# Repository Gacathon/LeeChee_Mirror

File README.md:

# Lisence

CC BY-NC-SA 3.0

# LeeChee_Mirror
Cherry G80&amp;G81-1800 Keyboard layout.Almost both sides place switch.

# Recommend
Please read Readme.docx before assembling.

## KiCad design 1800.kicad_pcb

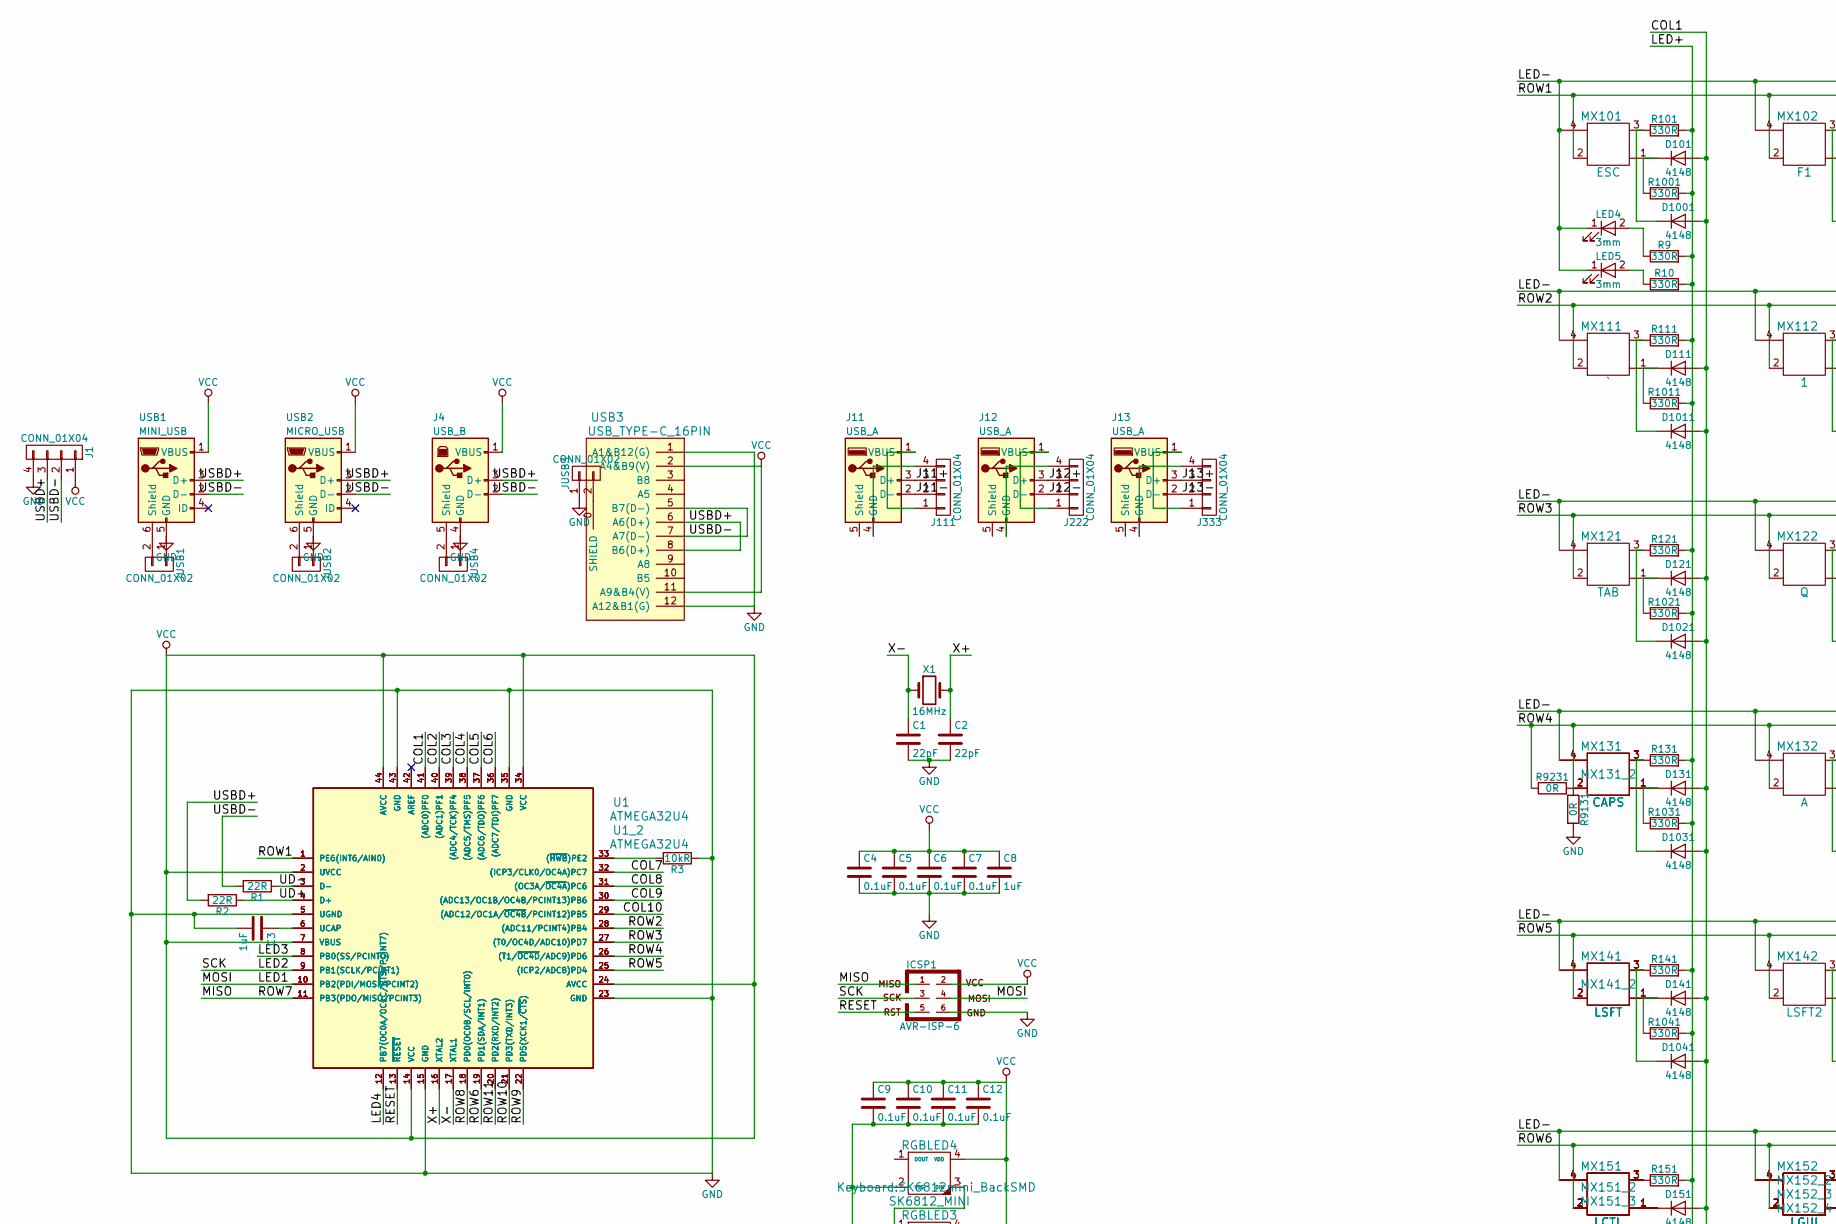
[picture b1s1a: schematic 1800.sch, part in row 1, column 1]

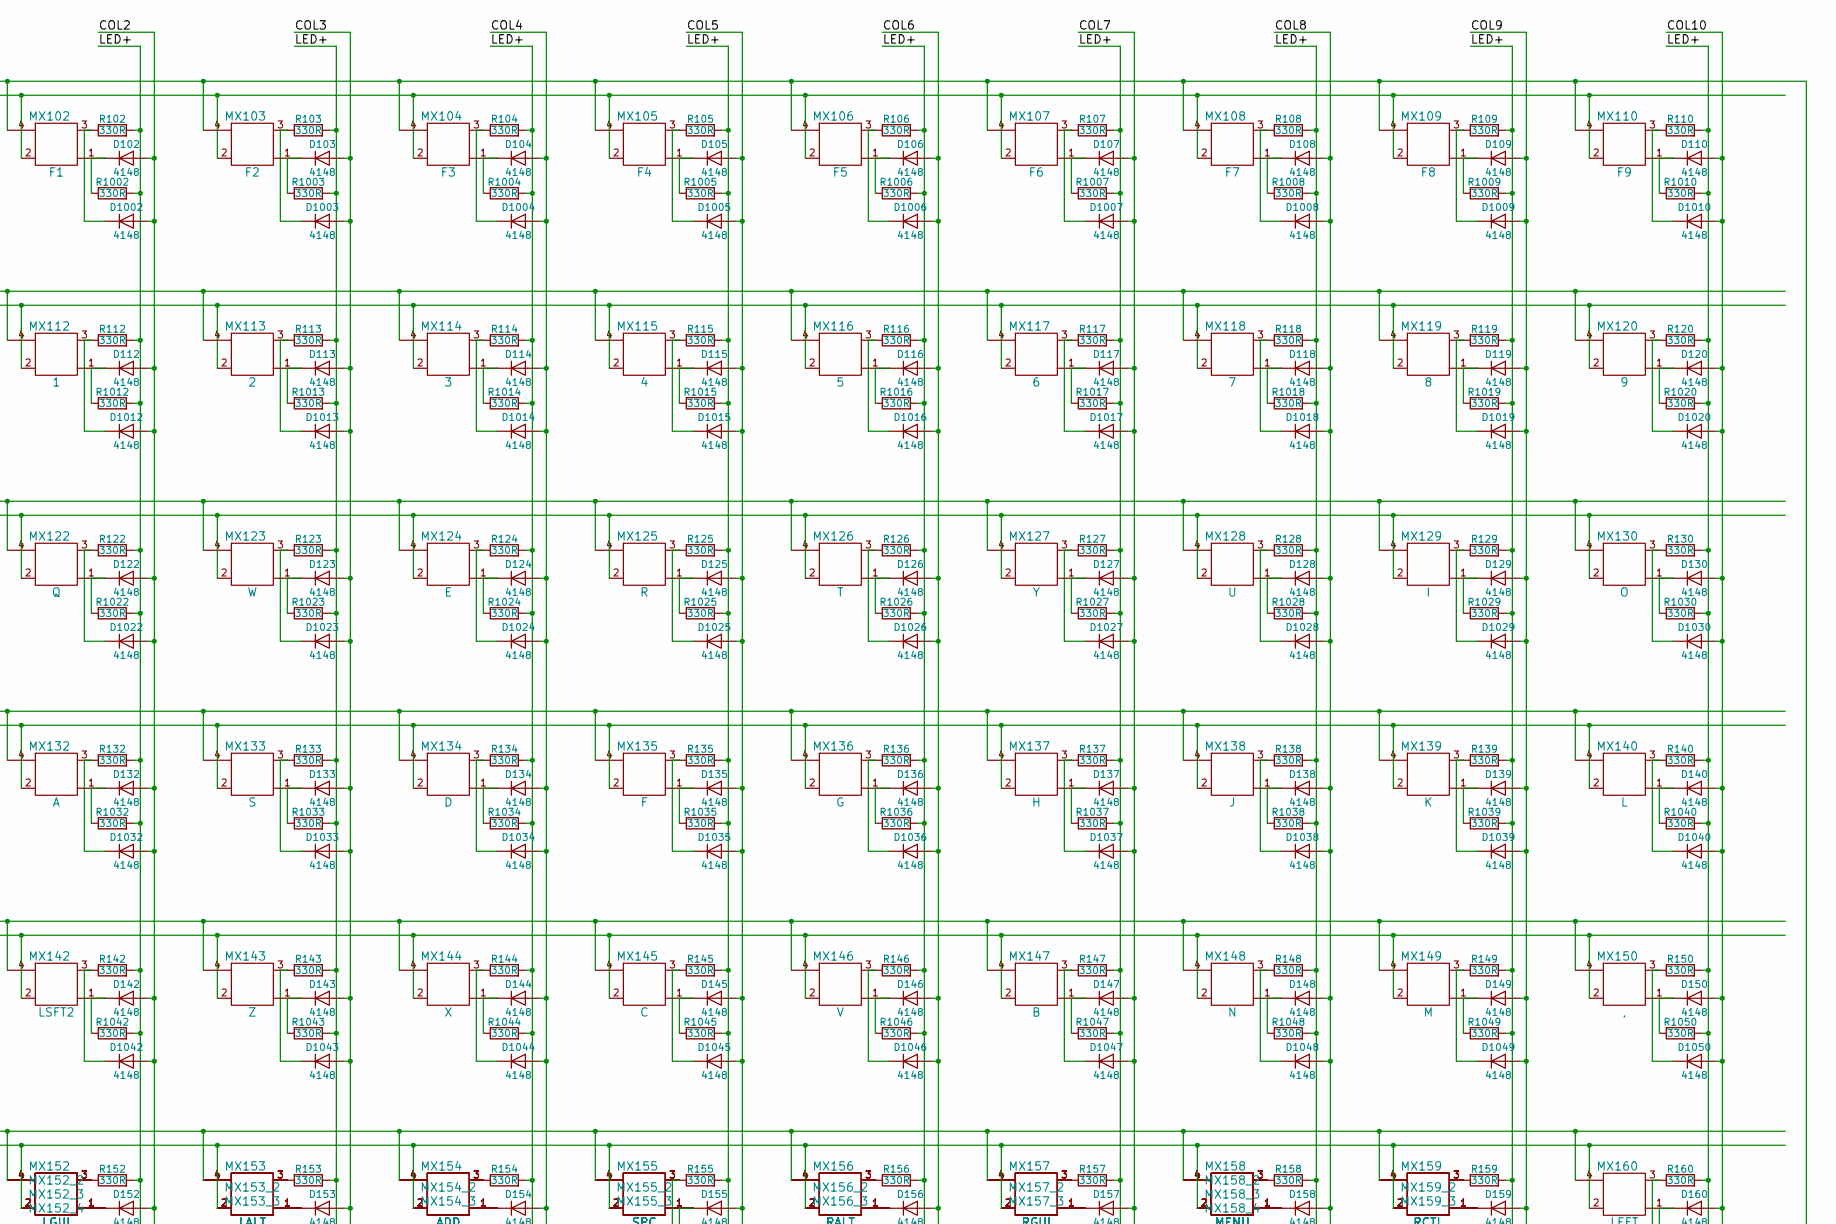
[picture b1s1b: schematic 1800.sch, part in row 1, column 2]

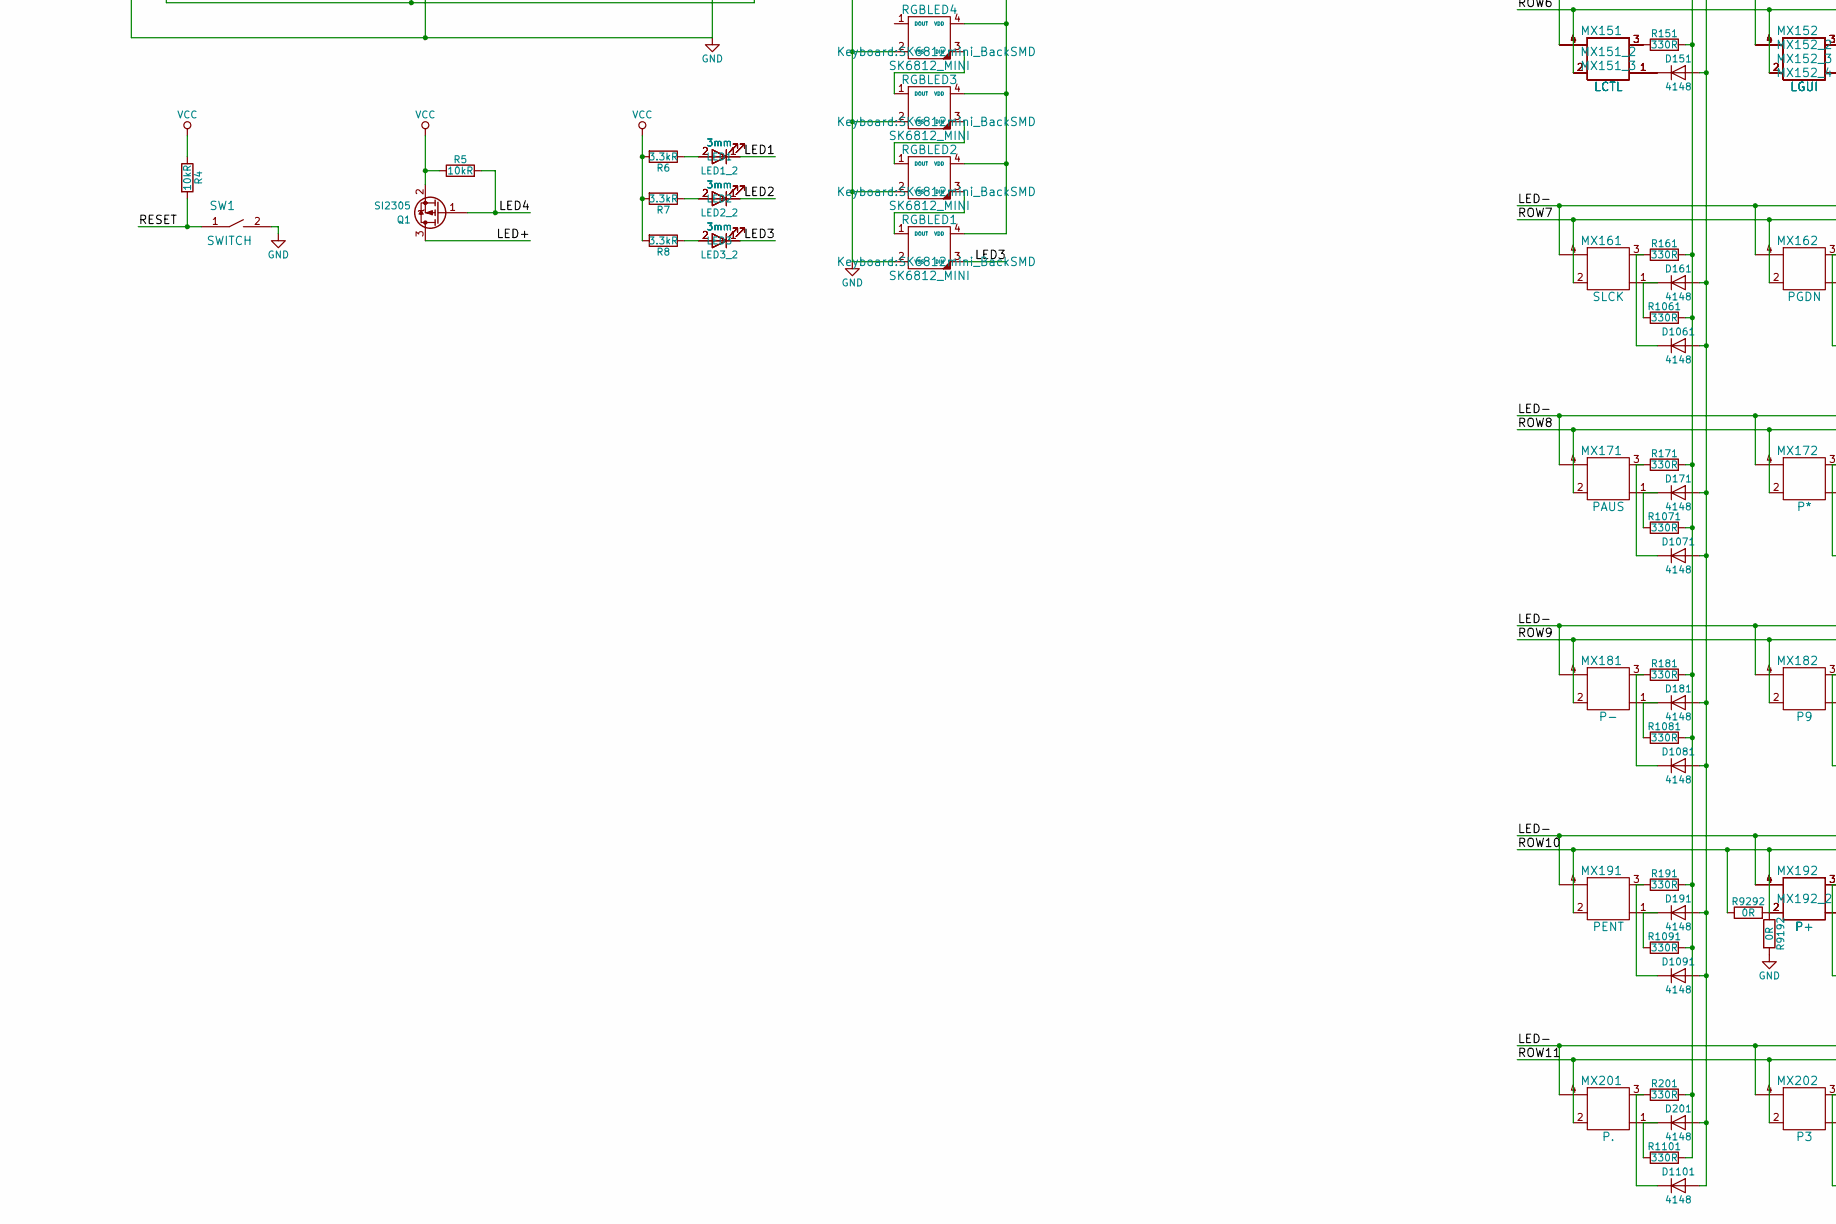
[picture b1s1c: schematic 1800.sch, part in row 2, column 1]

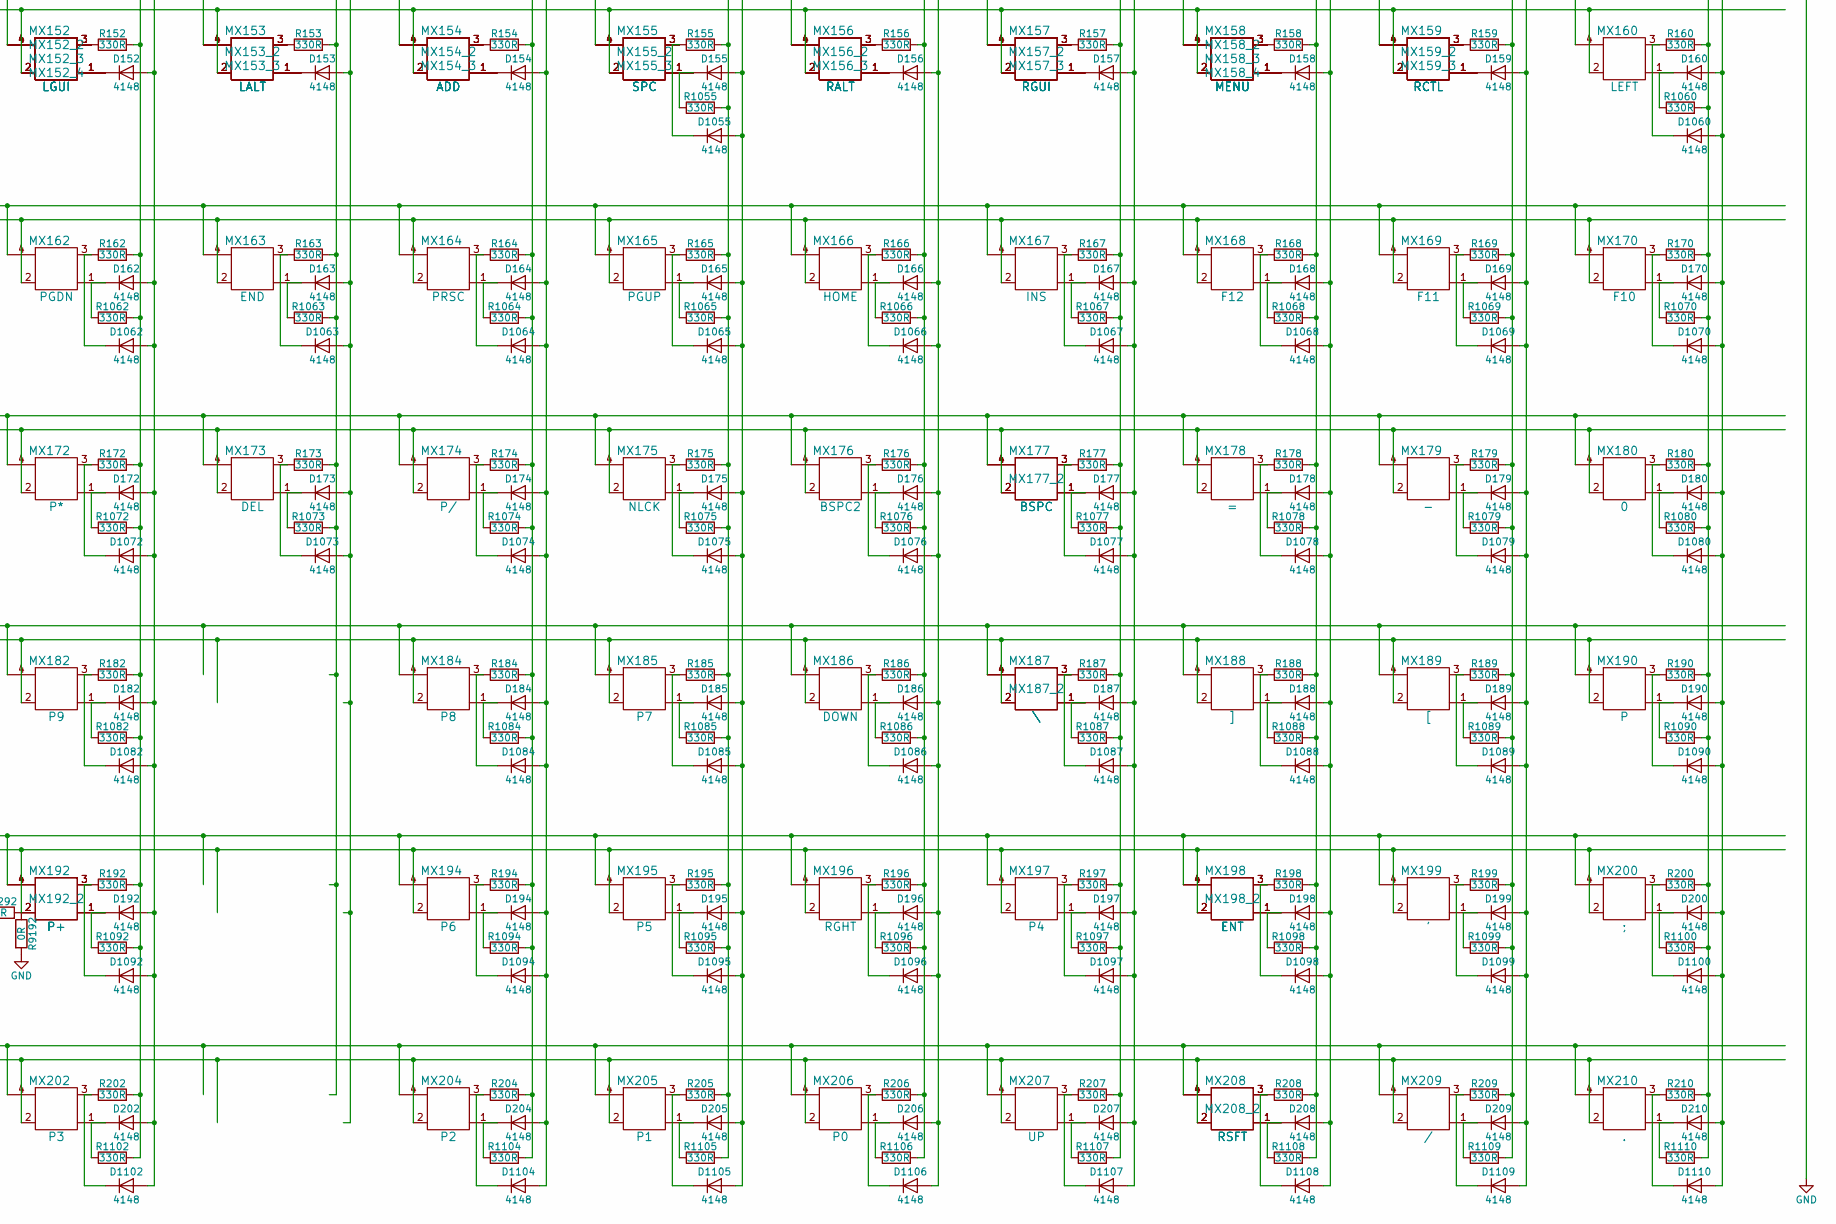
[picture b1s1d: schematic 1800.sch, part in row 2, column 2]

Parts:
C1, C2: 22pF; C_0805
C3, C8: 1uF; C_0805
C4, C5, C6, C7, C9, C10, C11, C12: 0.1uF; C_0805
D101, D102, D103, D104, D105, D106, D107, D108, D109, D110, D111, D112, D113, D114, D115, D116, D117, D118, D119, D120, D121, D122, D123, D124, D125, D126, D127, D128, D129, D130, D131, D132, D133, D134, D135, D136, D137, D138, D139, D140, D141, D142, D143, D144, D145, D146, D147, D148, D149, D150, D151, D152, D153, D154, D155, D156, D157, D158, D159, D160, D161, D162, D163, D164, D165, D166, D167, D168, D169, D170, D171, D172, D173, D174, D175, D176, D177, D178, D179, D180, D181, D182, D184, D185, D186, D187, D188, D189, D190, D191, D192, D194, D195, D196, D197, D198, D199, D200, D201, D202, D204, D205, D206, D207, D208, D209, D210, D1001, D1002, D1003, D1004, D1005, D1006, D1007, D1008, D1009, D1010, D1011, D1012, D1013, D1014, D1015, D1016, D1017, D1018, D1019, D1020, D1021, D1022, D1023, D1024, D1025, D1026, D1027, D1028, D1029, D1030, D1031, D1032, D1033, D1034, D1035, D1036, D1037, D1038, D1039, D1040, D1041, D1042, D1043, D1044, D1045, D1046, D1047, D1048, D1049, D1050, D1055, D1060, D1061, D1062, D1063, D1064, D1065, D1066, D1067, D1068, D1069, D1070, D1071, D1072, D1073, D1074, D1075, D1076, D1077, D1078, D1079, D1080, D1081, D1082, D1084, D1085, D1086, D1087, D1088, D1089, D1090, D1091, D1092, D1094, D1095, D1096, D1097, D1098, D1099, D1100, D1101, D1102, D1104, D1105, D1106, D1107, D1108, D1109, D1110: 4148; D_0805
ICSP1: AVR-ISP-6; Pin_Header_Straight_2x03_Pitch2.54mm
J1, J111, J222, J333: CONN_01X04; Pin_Header_Straight_1x04_Pitch2.54mm
J4: USB_B
J11, J12, J13: USB_A; USB_A_2
JUSB1, JUSB2, JUSB3, JUSB4: CONN_01X02; Pin_Header_Straight_1x02_Pitch1.27mm
LED1, LED1_2, LED2, LED2_2, LED3, LED3_2, LED4, LED5: 3mm; LED_D3.0mm
MX101: ESC; MX1A&LEDx2
MX102: F1; MX1A&LEDx2
MX103: F2; MX1A&LEDx2
MX104: F3; MX1A&LEDx2
MX105: F4; MX1A&LEDx2
MX106: F5; MX1A&LEDx2
MX107: F6; MX1A&LEDx2
MX108: F7; MX1A&LEDx2
MX109: F8; MX1A&LEDx2
MX110: F9; MX1A&LEDx2
MX111: `; MX1A&LEDx2
MX112: 1; MX1A&LEDx2
MX113: 2; MX1A&LEDx2
MX114: 3; MX1A&LEDx2
MX115: 4; MX1A&LEDx2
MX116: 5; MX1A&LEDx2
MX117: 6; MX1A&LEDx2
MX118: 7; MX1A&LEDx2
MX119: 8; MX1A&LEDx2
MX120: 9; MX1A&LEDx2
MX121: TAB; MX1A&LEDx2
MX122: Q; MX1A&LEDx2
MX123: W; MX1A&LEDx2
MX124: E; MX1A&LEDx2
MX125: R; MX1A&LEDx2
MX126: T; MX1A&LEDx2
MX127: Y; MX1A&LEDx2
MX128: U; MX1A&LEDx2
MX129: I; MX1A&LEDx2
MX130: O; MX1A&LEDx2
MX131, MX131_2: CAPS; MX1A&LEDx2
MX132: A; MX1A&LEDx2
MX133: S; MX1A&LEDx2
MX134: D; MX1A&LEDx2
MX135: F; MX1A&LEDx2
MX136: G; MX1A&LEDx2
MX137: H; MX1A&LEDx2
MX138: J; MX1A&LEDx2
MX139: K; MX1A&LEDx2
MX140: L; MX1A&LEDx2
MX141, MX141_2: LSFT; MX1A&LEDx2
MX142: LSFT2; MX1A&LEDx2
MX143: Z; MX1A&LEDx2
MX144: X; MX1A&LEDx2
MX145: C; MX1A&LEDx2
MX146: V; MX1A&LEDx2
MX147: B; MX1A&LEDx2
MX148: N; MX1A&LEDx2
MX149: M; MX1A&LEDx2
MX150: ,; MX1A&LEDx2
MX151, MX151_2, MX151_3: LCTL; MX1A&LED
MX152, MX152_2, MX152_3, MX152_4: LGUI; MX1A&LED
MX153, MX153_2, MX153_3: LALT; MX1A&LED
MX154, MX154_2, MX154_3: ADD; MX1A&LED
MX155, MX155_2, MX155_3: SPC; MX1A&LEDx2
MX156, MX156_2, MX156_3: RALT; MX1A&LED
MX157, MX157_2, MX157_3: RGUI; MX1A&LED
MX158, MX158_2, MX158_3, MX158_4: MENU; MX1A&LED
MX159, MX159_2, MX159_3: RCTL; MX1A&LED
MX160: LEFT; MX1A&LEDx2
MX161: SLCK; MX1A&LEDx2
MX162: PGDN; MX1A&LEDx2
MX163: END; MX1A&LEDx2
MX164: PRSC; MX1A&LEDx2
MX165: PGUP; MX1A&LEDx2
MX166: HOME; MX1A&LEDx2
MX167: INS; MX1A&LEDx2
MX168: F12; MX1A&LEDx2
MX169: F11; MX1A&LEDx2
MX170: F10; MX1A&LEDx2
MX171: PAUS; MX1A&LEDx2
MX172: P*; MX1A&LEDx2
MX173: DEL; MX1A&LEDx2
MX174: P/; MX1A&LEDx2
MX175: NLCK; MX1A&LEDx2
MX176: BSPC2; MX1A&LEDx2
MX177, MX177_2: BSPC; MX1A&LEDx2
MX178: =; MX1A&LEDx2
MX179: -; MX1A&LEDx2
MX180: 0; MX1A&LEDx2
MX181: P-; MX1A&LEDx2
MX182: P9; MX1A&LEDx2
MX184: P8; MX1A&LEDx2
MX185: P7; MX1A&LEDx2
MX186: DOWN; MX1A&LEDx2
MX187, MX187_2: \\; MX1A&LEDx2
MX188: ]; MX1A&LEDx2
MX189: [; MX1A&LEDx2
MX190: P; MX1A&LEDx2
MX191: PENT; MX1A&LEDx2
MX192, MX192_2: P+; MX1A&LEDx2
MX194: P6; MX1A&LEDx2
MX195: P5; MX1A&LEDx2
MX196: RGHT; MX1A&LEDx2
MX197: P4; MX1A&LEDx2
MX198, MX198_2: ENT; MX1A&LEDx2
MX199: '; MX1A&LEDx2
MX200: ;; MX1A&LEDx2
MX201: P.; MX1A&LEDx2
MX202: P3; MX1A&LEDx2
MX204: P2; MX1A&LEDx2
MX205: P1; MX1A&LEDx2
MX206: P0; MX1A&LEDx2
MX207: UP; MX1A&LEDx2
MX208, MX208_2: RSFT; MX1A&LEDx2
MX209: /; MX1A&LEDx2
MX210: .; MX1A&LEDx2
Q1: SI2305; SOT-23
R1, R2: 22R; R_0805
R3, R4, R5: 10kR; R_0805
R6, R7, R8: 3.3kR; R_0805
R9, R10, R101, R102, R103, R104, R105, R106, R107, R108, R109, R110, R111, R112, R113, R114, R115, R116, R117, R118, R119, R120, R121, R122, R123, R124, R125, R126, R127, R128, R129, R130, R131, R132, R133, R134, R135, R136, R137, R138, R139, R140, R141, R142, R143, R144, R145, R146, R147, R148, R149, R150, R151, R152, R153, R154, R155, R156, R157, R158, R159, R160, R161, R162, R163, R164, R165, R166, R167, R168, R169, R170, R171, R172, R173, R174, R175, R176, R177, R178, R179, R180, R181, R182, R184, R185, R186, R187, R188, R189, R190, R191, R192, R194, R195, R196, R197, R198, R199, R200, R201, R202, R204, R205, R206, R207, R208, R209, R210, R1001, R1002, R1003, R1004, R1005, R1006, R1007, R1008, R1009, R1010, R1011, R1012, R1013, R1014, R1015, R1016, R1017, R1018, R1019, R1020, R1021, R1022, R1023, R1024, R1025, R1026, R1027, R1028, R1029, R1030, R1031, R1032, R1033, R1034, R1035, R1036, R1037, R1038, R1039, R1040, R1041, R1042, R1043, R1044, R1045, R1046, R1047, R1048, R1049, R1050, R1055, R1060, R1061, R1062, R1063, R1064, R1065, R1066, R1067, R1068, R1069, R1070, R1071, R1072, R1073, R1074, R1075, R1076, R1077, R1078, R1079, R1080, R1081, R1082, R1084, R1085, R1086, R1087, R1088, R1089, R1090, R1091, R1092, R1094, R1095, R1096, R1097, R1098, R1099, R1100, R1101, R1102, R1104, R1105, R1106, R1107, R1108, R1109, R1110: 330R; R_0805
R9131, R9192, R9231, R9292: 0R; R_0805
RGBLED1, RGBLED2, RGBLED3, RGBLED4: SK6812_MINI; SK6812mini_BackSMD
SW1: SWITCH; SWITCH-3X6X2.5_SMD+
U1: ATMEGA32U4; TQFP-44_10x10mm_Pitch0.8mm
U1_2: ATMEGA32U4; QFN-44_7x7mm_Pitch0.5mm
USB1: MINI_USB; USB_MINI_4FOOT
USB2: MICRO_USB; USB_MICRO_4FOOT
USB3: USB_TYPE-C_16PIN
X1: 16MHz; Crystal_SMD_5032-2pin_5.0x3.2mm

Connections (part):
/COL1: D101.2 (A), D111.2 (A), D121.2 (A), D131.2 (A), D141.2 (A), D151.2 (A), D161.2 (A), D171.2 (A), D181.2 (A), D191.2 (A), D201.2 (A), D1001.2 (A), D1011.2 (A), D1021.2 (A), D1031.2 (A), D1041.2 (A), D1061.2 (A), D1071.2 (A), D1081.2 (A), D1091.2 (A), D1101.2 (A), U1.41 ((ADC0)PF0), U1_2.41 ((ADC0)PF0)
/COL2: D102.2 (A), D112.2 (A), D122.2 (A), D132.2 (A), D142.2 (A), D152.2 (A), D162.2 (A), D172.2 (A), D182.2 (A), D192.2 (A), D202.2 (A), D1002.2 (A), D1012.2 (A), D1022.2 (A), D1032.2 (A), D1042.2 (A), D1062.2 (A), D1072.2 (A), D1082.2 (A), D1092.2 (A), D1102.2 (A), U1.40 ((ADC1)PF1), U1_2.40 ((ADC1)PF1)
/COL3: D103.2 (A), D113.2 (A), D123.2 (A), D133.2 (A), D143.2 (A), D153.2 (A), D163.2 (A), D173.2 (A), D1003.2 (A), D1013.2 (A), D1023.2 (A), D1033.2 (A), D1043.2 (A), D1063.2 (A), D1073.2 (A), U1.39 ((ADC4/TCK)PF4), U1_2.39 ((ADC4/TCK)PF4)
/COL4: D104.2 (A), D114.2 (A), D124.2 (A), D134.2 (A), D144.2 (A), D154.2 (A), D164.2 (A), D174.2 (A), D184.2 (A), D194.2 (A), D204.2 (A), D1004.2 (A), D1014.2 (A), D1024.2 (A), D1034.2 (A), D1044.2 (A), D1064.2 (A), D1074.2 (A), D1084.2 (A), D1094.2 (A), D1104.2 (A), U1.38 ((ADC5/TMS)PF5), U1_2.38 ((ADC5/TMS)PF5)
/COL5: D105.2 (A), D115.2 (A), D125.2 (A), D135.2 (A), D145.2 (A), D155.2 (A), D165.2 (A), D175.2 (A), D185.2 (A), D195.2 (A), D205.2 (A), D1005.2 (A), D1015.2 (A), D1025.2 (A), D1035.2 (A), D1045.2 (A), D1055.2 (A), D1065.2 (A), D1075.2 (A), D1085.2 (A), D1095.2 (A), D1105.2 (A), U1.37 ((ADC6/TDO)PF6), U1_2.37 ((ADC6/TDO)PF6)
/COL6: D106.2 (A), D116.2 (A), D126.2 (A), D136.2 (A), D146.2 (A), D156.2 (A), D166.2 (A), D176.2 (A), D186.2 (A), D196.2 (A), D206.2 (A), D1006.2 (A), D1016.2 (A), D1026.2 (A), D1036.2 (A), D1046.2 (A), D1066.2 (A), D1076.2 (A), D1086.2 (A), D1096.2 (A), D1106.2 (A), U1.36 ((ADC7/TDI)PF7), U1_2.36 ((ADC7/TDI)PF7)
/COL7: D107.2 (A), D117.2 (A), D127.2 (A), D137.2 (A), D147.2 (A), D157.2 (A), D167.2 (A), D177.2 (A), D187.2 (A), D197.2 (A), D207.2 (A), D1007.2 (A), D1017.2 (A), D1027.2 (A), D1037.2 (A), D1047.2 (A), D1067.2 (A), D1077.2 (A), D1087.2 (A), D1097.2 (A), D1107.2 (A), U1.32 ((ICP3/CLK0/OC4A)PC7), U1_2.32 ((ICP3/CLK0/OC4A)PC7)
/COL8: D108.2 (A), D118.2 (A), D128.2 (A), D138.2 (A), D148.2 (A), D158.2 (A), D168.2 (A), D178.2 (A), D188.2 (A), D198.2 (A), D208.2 (A), D1008.2 (A), D1018.2 (A), D1028.2 (A), D1038.2 (A), D1048.2 (A), D1068.2 (A), D1078.2 (A), D1088.2 (A), D1098.2 (A), D1108.2 (A), U1.31 ((OC3A/~OC4A~)PC6), U1_2.31 ((OC3A/~OC4A~)PC6)
/COL9: D109.2 (A), D119.2 (A), D129.2 (A), D139.2 (A), D149.2 (A), D159.2 (A), D169.2 (A), D179.2 (A), D189.2 (A), D199.2 (A), D209.2 (A), D1009.2 (A), D1019.2 (A), D1029.2 (A), D1039.2 (A), D1049.2 (A), D1069.2 (A), D1079.2 (A), D1089.2 (A), D1099.2 (A), D1109.2 (A), U1.30 ((ADC13/OC1B/OC4B/PCINT13)PB6), U1_2.30 ((ADC13/OC1B/OC4B/PCINT13)PB6)
/COL10: D110.2 (A), D120.2 (A), D130.2 (A), D140.2 (A), D150.2 (A), D160.2 (A), D170.2 (A), D180.2 (A), D190.2 (A), D200.2 (A), D210.2 (A), D1010.2 (A), D1020.2 (A), D1030.2 (A), D1040.2 (A), D1050.2 (A), D1060.2 (A), D1070.2 (A), D1080.2 (A), D1090.2 (A), D1100.2 (A), D1110.2 (A), U1.29 ((ADC12/OC1A/~OC4B~/PCINT12)PB5), U1_2.29 ((ADC12/OC1A/~OC4B~/PCINT12)PB5)
/J11+: J11.3 (D+), J111.3
/J11-: J11.2 (D-), J111.2
/J12+: J12.3 (D+), J222.3
/J12-: J12.2 (D-), J222.2
/J13+: J13.3 (D+), J333.3
/J13-: J13.2 (D-), J333.2
/LED1: ICSP1.4, LED1.1 (K), LED1_2.1 (K), U1.10 (PB2(PDI/MOSI/PCINT2)), U1_2.10 (PB2(PDI/MOSI/PCINT2))
/LED2: ICSP1.3, LED2.1 (K), LED2_2.1 (K), U1.9 (PB1(SCLK/PCINT1)), U1_2.9 (PB1(SCLK/PCINT1))
/LED3: LED3.1 (K), LED3_2.1 (K), RGBLED1.3 (DIN), U1.8 (PB0(SS/PCINT0)), U1_2.8 (PB0(SS/PCINT0))
/LED4: Q1.1 (G), R5.2, U1.12 (PB7(OC0A/OC1C/~RTS~/PCINT7)), U1_2.12 (PB7(OC0A/OC1C/~RTS~/PCINT7))
/LED+: Q1.3 (D), R9.2, R10.2, R101.2, R102.2, R103.2, R104.2, R105.2, R106.2, R107.2, R108.2, R109.2, R110.2, R111.2, R112.2, R113.2, R114.2, R115.2, R116.2, R117.2, R118.2, R119.2, R120.2, R121.2, R122.2, R123.2, R124.2, R125.2, R126.2, R127.2, R128.2, R129.2, R130.2, R131.2, R132.2, R133.2, R134.2, R135.2, R136.2, R137.2, R138.2, R139.2, R140.2, R141.2, R142.2, R143.2, R144.2, R145.2, R146.2, R147.2, R148.2, R149.2, R150.2, R151.2, R152.2, R153.2, R154.2, R155.2, R156.2, R157.2, R158.2, R159.2, R160.2, R161.2, R162.2, R163.2, R164.2, R165.2, R166.2, R167.2, R168.2, R169.2, R170.2, R171.2, R172.2, R173.2, R174.2, R175.2, R176.2, R177.2, R178.2, R179.2, R180.2, R181.2, R182.2, R184.2, R185.2, R186.2, R187.2, R188.2, R189.2, R190.2, R191.2, R192.2, R194.2, R195.2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
/MISO: ICSP1.1, MX161.2, MX162.2, MX163.2, MX164.2, MX165.2, MX166.2, MX167.2, MX168.2, MX169.2, MX170.2, U1.11 (PB3(PDO/MISO/PCINT3)), U1_2.11 (PB3(PDO/MISO/PCINT3))
/RESET: ICSP1.5, R4.2, SW1.1, U1.13 (~RESET~), U1_2.13 (~RESET~)
/ROW1: MX101.2, MX102.2, MX103.2, MX104.2, MX105.2, MX106.2, MX107.2, MX108.2, MX109.2, MX110.2, U1.1 (PE6(INT6/AIN0)), U1_2.1 (PE6(INT6/AIN0))
/ROW2: MX111.2, MX112.2, MX113.2, MX114.2, MX115.2, MX116.2, MX117.2, MX118.2, MX119.2, MX120.2, U1.28 ((ADC11/PCINT4)PB4), U1_2.28 ((ADC11/PCINT4)PB4)
/ROW3: MX121.2, MX122.2, MX123.2, MX124.2, MX125.2, MX126.2, MX127.2, MX128.2, MX129.2, MX130.2, U1.27 ((T0/OC4D/ADC10)PD7), U1_2.27 ((T0/OC4D/ADC10)PD7)
/ROW4: MX131.2, MX131_2.2, MX132.2, MX133.2, MX134.2, MX135.2, MX136.2, MX137.2, MX138.2, MX139.2, MX140.2, R9131.1, R9231.1, R9231.2, U1.26 ((T1/~OC4D~/ADC9)PD6), U1_2.26 ((T1/~OC4D~/ADC9)PD6)
/ROW5: MX141.2, MX141_2.2, MX142.2, MX143.2, MX144.2, MX145.2, MX146.2, MX147.2, MX148.2, MX149.2, MX150.2, U1.25 ((ICP2/ADC8)PD4), U1_2.25 ((ICP2/ADC8)PD4)
/ROW6: MX151.2, MX151_2.2, MX151_3.2, MX152.2, MX152_2.2, MX152_3.2, MX152_4.2, MX153.2, MX153_2.2, MX153_3.2, MX154.2, MX154_2.2, MX154_3.2, MX155.2, MX155_2.2, MX155_3.2, MX156.2, MX156_2.2, MX156_3.2, MX157.2, MX157_2.2, MX157_3.2, MX158.2, MX158_2.2, MX158_3.2, MX158_4.2, MX159.2, MX159_2.2, MX159_3.2, MX160.2, U1.19 (PD1(SDA/INT1)), U1_2.19 (PD1(SDA/INT1))
/ROW8: MX171.2, MX172.2, MX173.2, MX174.2, MX175.2, MX176.2, MX177.2, MX177_2.2, MX178.2, MX179.2, MX180.2, U1.18 (PD0(OC0B/SCL/INT0)), U1_2.18 (PD0(OC0B/SCL/INT0))
/ROW9: MX181.2, MX182.2, MX184.2, MX185.2, MX186.2, MX187.2, MX187_2.2, MX188.2, MX189.2, MX190.2, U1.22 (PD5(XCK1/~CTS~)), U1_2.22 (PD5(XCK1/~CTS~))
/ROW10: MX191.2, MX192.2, MX192_2.2, MX194.2, MX195.2, MX196.2, MX197.2, MX198.2, MX198_2.2, MX199.2, MX200.2, R9192.1, R9292.1, R9292.2, U1.21 (PD3(TXD/INT3)), U1_2.21 (PD3(TXD/INT3))
/ROW11: MX201.2, MX202.2, MX204.2, MX205.2, MX206.2, MX207.2, MX208.2, MX208_2.2, MX209.2, MX210.2, U1.20 (PD2(RXD/INT2)), U1_2.20 (PD2(RXD/INT2))
/UD+: R2.1, U1.4 (D+), U1_2.4 (D+)
/UD-: R1.1, U1.3 (D-), U1_2.3 (D-)
/USBD+: J1.3, J4.3 (D+), R2.2, USB1.3 (D+), USB2.3 (D+), USB3.6 (A6(D+)), USB3.8 (B6(D+)); also elsewhere on the board
/USBD-: J1.2, J4.2 (D-), R1.2, USB1.2 (D-), USB2.2 (D-), USB3.5 (B7(D-)), USB3.7 (A7(D-)); also elsewhere on the board
/X+: C2.1, U1.16 (XTAL2), U1_2.16 (XTAL2), X1.2
/X-: C1.1, U1.17 (XTAL1), U1_2.17 (XTAL1), X1.1
GND: C1.2, C2.2, C3.2, C4.2, C5.2, C6.2, C7.2, C8.2, C9.2, C10.2, C11.2, C12.2, ICSP1.6, J1.4, J4.4 (GND), JUSB1.1, JUSB2.1, JUSB3.1, JUSB4.1, LED4.1 (K), LED5.1 (K), MX101.4, MX102.4, MX103.4, MX104.4, MX105.4, MX106.4, MX107.4, MX108.4, MX109.4, MX110.4, MX111.4, MX112.4, MX113.4, MX114.4, MX115.4, MX116.4, MX117.4, MX118.4, MX119.4, MX120.4, MX121.4, MX122.4, MX123.4, MX124.4, MX125.4, MX126.4, MX127.4, MX128.4, MX129.4, MX130.4, MX131.4, MX131_2.4, MX132.4, MX133.4, MX134.4, MX135.4, MX136.4, MX137.4, MX138.4, MX139.4, MX140.4, MX141.4, MX141_2.4, MX142.4, MX143.4, MX144.4, MX145.4, MX146.4, MX147.4, MX148.4, MX149.4, MX150.4, MX151.4, MX151_2.4, MX151_3.4, MX152.4, MX152_2.4, MX152_3.4, MX152_4.4, MX153.4, MX153_2.4, MX153_3.4, MX154.4, MX154_2.4, MX154_3.4, MX155.4, MX155_2.4, MX155_3.4, MX156.4, MX156_2.4, MX156_3.4, MX157.4, MX157_2.4, MX157_3.4, MX158.4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; also elsewhere on the board
unnamed: C3.1, U1.6 (UCAP), U1_2.6 (UCAP)
unnamed: D101.1 (K), MX101.1, R1001.1
unnamed: D102.1 (K), MX102.1, R1002.1
unnamed: D103.1 (K), MX103.1, R1003.1
unnamed: D104.1 (K), MX104.1, R1004.1
unnamed: D105.1 (K), MX105.1, R1005.1
unnamed: D106.1 (K), MX106.1, R1006.1
unnamed: D107.1 (K), MX107.1, R1007.1
unnamed: D108.1 (K), MX108.1, R1008.1
unnamed: D109.1 (K), MX109.1, R1009.1
unnamed: D110.1 (K), MX110.1, R1010.1
unnamed: D111.1 (K), MX111.1, R1011.1
unnamed: D112.1 (K), MX112.1, R1012.1
unnamed: D113.1 (K), MX113.1, R1013.1
unnamed: D114.1 (K), MX114.1, R1014.1
unnamed: D115.1 (K), MX115.1, R1015.1
unnamed: D116.1 (K), MX116.1, R1016.1
unnamed: D117.1 (K), MX117.1, R1017.1
unnamed: D118.1 (K), MX118.1, R1018.1
unnamed: D119.1 (K), MX119.1, R1019.1
unnamed: D120.1 (K), MX120.1, R1020.1
unnamed: D121.1 (K), MX121.1, R1021.1
unnamed: D122.1 (K), MX122.1, R1022.1
unnamed: D123.1 (K), MX123.1, R1023.1
unnamed: D124.1 (K), MX124.1, R1024.1
unnamed: D125.1 (K), MX125.1, R1025.1
unnamed: D126.1 (K), MX126.1, R1026.1
unnamed: D127.1 (K), MX127.1, R1027.1
unnamed: D128.1 (K), MX128.1, R1028.1
unnamed: D129.1 (K), MX129.1, R1029.1
unnamed: D130.1 (K), MX130.1, R1030.1
unnamed: D131.1 (K), MX131.1, MX131_2.1, R1031.1
unnamed: D132.1 (K), MX132.1, R1032.1
unnamed: D133.1 (K), MX133.1, R1033.1
unnamed: D134.1 (K), MX134.1, R1034.1
unnamed: D135.1 (K), MX135.1, R1035.1
unnamed: D136.1 (K), MX136.1, R1036.1
unnamed: D137.1 (K), MX137.1, R1037.1
unnamed: D138.1 (K), MX138.1, R1038.1
unnamed: D139.1 (K), MX139.1, R1039.1
unnamed: D140.1 (K), MX140.1, R1040.1
unnamed: D141.1 (K), MX141.1, MX141_2.1, R1041.1
unnamed: D142.1 (K), MX142.1, R1042.1
unnamed: D143.1 (K), MX143.1, R1043.1
unnamed: D144.1 (K), MX144.1, R1044.1
unnamed: D145.1 (K), MX145.1, R1045.1
unnamed: D146.1 (K), MX146.1, R1046.1
unnamed: D147.1 (K), MX147.1, R1047.1
unnamed: D148.1 (K), MX148.1, R1048.1
unnamed: D149.1 (K), MX149.1, R1049.1
unnamed: D150.1 (K), MX150.1, R1050.1
unnamed: D151.1 (K), MX151.1, MX151_2.1, MX151_3.1
unnamed: D152.1 (K), MX152.1, MX152_2.1, MX152_3.1, MX152_4.1
unnamed: D153.1 (K), MX153.1, MX153_2.1, MX153_3.1
unnamed: D154.1 (K), MX154.1, MX154_2.1, MX154_3.1
unnamed: D155.1 (K), MX155.1, MX155_2.1, MX155_3.1, R1055.1
unnamed: D156.1 (K), MX156.1, MX156_2.1, MX156_3.1
unnamed: D157.1 (K), MX157.1, MX157_2.1, MX157_3.1
unnamed: D158.1 (K), MX158.1, MX158_2.1, MX158_3.1, MX158_4.1
unnamed: D159.1 (K), MX159.1, MX159_2.1, MX159_3.1
unnamed: D160.1 (K), MX160.1, R1060.1
unnamed: D161.1 (K), MX161.1, R1061.1
unnamed: D162.1 (K), MX162.1, R1062.1
unnamed: D163.1 (K), MX163.1, R1063.1
unnamed: D164.1 (K), MX164.1, R1064.1
unnamed: D165.1 (K), MX165.1, R1065.1
unnamed: D166.1 (K), MX166.1, R1066.1
unnamed: D167.1 (K), MX167.1, R1067.1
unnamed: D168.1 (K), MX168.1, R1068.1
unnamed: D169.1 (K), MX169.1, R1069.1
unnamed: D170.1 (K), MX170.1, R1070.1
unnamed: D171.1 (K), MX171.1, R1071.1
unnamed: D172.1 (K), MX172.1, R1072.1
unnamed: D173.1 (K), MX173.1, R1073.1
unnamed: D174.1 (K), MX174.1, R1074.1
unnamed: D175.1 (K), MX175.1, R1075.1
unnamed: D176.1 (K), MX176.1, R1076.1
unnamed: D177.1 (K), MX177.1, MX177_2.1, R1077.1
unnamed: D178.1 (K), MX178.1, R1078.1
unnamed: D179.1 (K), MX179.1, R1079.1
unnamed: D180.1 (K), MX180.1, R1080.1
unnamed: D181.1 (K), MX181.1, R1081.1
unnamed: D182.1 (K), MX182.1, R1082.1
unnamed: D184.1 (K), MX184.1, R1084.1
unnamed: D185.1 (K), MX185.1, R1085.1
unnamed: D186.1 (K), MX186.1, R1086.1
unnamed: D187.1 (K), MX187.1, MX187_2.1, R1087.1
unnamed: D188.1 (K), MX188.1, R1088.1
unnamed: D189.1 (K), MX189.1, R1089.1
unnamed: D190.1 (K), MX190.1, R1090.1
unnamed: D191.1 (K), MX191.1, R1091.1
unnamed: D192.1 (K), MX192.1, MX192_2.1, R1092.1
unnamed: D194.1 (K), MX194.1, R1094.1
unnamed: D195.1 (K), MX195.1, R1095.1
unnamed: D196.1 (K), MX196.1, R1096.1
unnamed: D197.1 (K), MX197.1, R1097.1
unnamed: D198.1 (K), MX198.1, MX198_2.1, R1098.1
unnamed: D199.1 (K), MX199.1, R1099.1
unnamed: D200.1 (K), MX200.1, R1100.1
unnamed: D201.1 (K), MX201.1, R1101.1
unnamed: D202.1 (K), MX202.1, R1102.1
unnamed: D204.1 (K), MX204.1, R1104.1
unnamed: D205.1 (K), MX205.1, R1105.1
unnamed: D206.1 (K), MX206.1, R1106.1
unnamed: D207.1 (K), MX207.1, R1107.1
unnamed: D208.1 (K), MX208.1, MX208_2.1, R1108.1
unnamed: D209.1 (K), MX209.1, R1109.1
unnamed: D210.1 (K), MX210.1, R1110.1
unnamed: D1001.1 (K), MX101.3, R101.1
unnamed: D1002.1 (K), MX102.3, R102.1
unnamed: D1003.1 (K), MX103.3, R103.1
unnamed: D1004.1 (K), MX104.3, R104.1
unnamed: D1005.1 (K), MX105.3, R105.1
unnamed: D1006.1 (K), MX106.3, R106.1
unnamed: D1007.1 (K), MX107.3, R107.1
unnamed: D1008.1 (K), MX108.3, R108.1
unnamed: D1009.1 (K), MX109.3, R109.1
unnamed: D1010.1 (K), MX110.3, R110.1
unnamed: D1011.1 (K), MX111.3, R111.1
unnamed: D1012.1 (K), MX112.3, R112.1
unnamed: D1013.1 (K), MX113.3, R113.1
unnamed: D1014.1 (K), MX114.3, R114.1
unnamed: D1015.1 (K), MX115.3, R115.1
unnamed: D1016.1 (K), MX116.3, R116.1
unnamed: D1017.1 (K), MX117.3, R117.1
unnamed: D1018.1 (K), MX118.3, R118.1
unnamed: D1019.1 (K), MX119.3, R119.1
unnamed: D1020.1 (K), MX120.3, R120.1
unnamed: D1021.1 (K), MX121.3, R121.1
unnamed: D1022.1 (K), MX122.3, R122.1
unnamed: D1023.1 (K), MX123.3, R123.1
unnamed: D1024.1 (K), MX124.3, R124.1
unnamed: D1025.1 (K), MX125.3, R125.1
unnamed: D1026.1 (K), MX126.3, R126.1
unnamed: D1027.1 (K), MX127.3, R127.1
unnamed: D1028.1 (K), MX128.3, R128.1
unnamed: D1029.1 (K), MX129.3, R129.1
unnamed: D1030.1 (K), MX130.3, R130.1
unnamed: D1031.1 (K), MX131.3, MX131_2.3, R131.1
unnamed: D1032.1 (K), MX132.3, R132.1
unnamed: D1033.1 (K), MX133.3, R133.1
unnamed: D1034.1 (K), MX134.3, R134.1
unnamed: D1035.1 (K), MX135.3, R135.1
unnamed: D1036.1 (K), MX136.3, R136.1
unnamed: D1037.1 (K), MX137.3, R137.1
unnamed: D1038.1 (K), MX138.3, R138.1
unnamed: D1039.1 (K), MX139.3, R139.1
unnamed: D1040.1 (K), MX140.3, R140.1
unnamed: D1041.1 (K), MX141.3, MX141_2.3, R141.1
unnamed: D1042.1 (K), MX142.3, R142.1
unnamed: D1043.1 (K), MX143.3, R143.1
unnamed: D1044.1 (K), MX144.3, R144.1
unnamed: D1045.1 (K), MX145.3, R145.1
unnamed: D1046.1 (K), MX146.3, R146.1
unnamed: D1047.1 (K), MX147.3, R147.1
unnamed: D1048.1 (K), MX148.3, R148.1
unnamed: D1049.1 (K), MX149.3, R149.1
unnamed: D1050.1 (K), MX150.3, R150.1
unnamed: D1055.1 (K), MX155.3, MX155_2.3, MX155_3.3, R155.1
unnamed: D1060.1 (K), MX160.3, R160.1
unnamed: D1061.1 (K), MX161.3, R161.1
unnamed: D1062.1 (K), MX162.3, R162.1
unnamed: D1063.1 (K), MX163.3, R163.1
unnamed: D1064.1 (K), MX164.3, R164.1
unnamed: D1065.1 (K), MX165.3, R165.1
unnamed: D1066.1 (K), MX166.3, R166.1
unnamed: D1067.1 (K), MX167.3, R167.1
unnamed: D1068.1 (K), MX168.3, R168.1
unnamed: D1069.1 (K), MX169.3, R169.1
unnamed: D1070.1 (K), MX170.3, R170.1
unnamed: D1071.1 (K), MX171.3, R171.1
unnamed: D1072.1 (K), MX172.3, R172.1
unnamed: D1073.1 (K), MX173.3, R173.1
unnamed: D1074.1 (K), MX174.3, R174.1
unnamed: D1075.1 (K), MX175.3, R175.1
unnamed: D1076.1 (K), MX176.3, R176.1
unnamed: D1077.1 (K), MX177.3, MX177_2.3, R177.1
unnamed: D1078.1 (K), MX178.3, R178.1
unnamed: D1079.1 (K), MX179.3, R179.1
unnamed: D1080.1 (K), MX180.3, R180.1
unnamed: D1081.1 (K), MX181.3, R181.1
unnamed: D1082.1 (K), MX182.3, R182.1
unnamed: D1084.1 (K), MX184.3, R184.1
unnamed: D1085.1 (K), MX185.3, R185.1
unnamed: D1086.1 (K), MX186.3, R186.1
unnamed: D1087.1 (K), MX187.3, MX187_2.3, R187.1
unnamed: D1088.1 (K), MX188.3, R188.1
unnamed: D1089.1 (K), MX189.3, R189.1
unnamed: D1090.1 (K), MX190.3, R190.1
unnamed: D1091.1 (K), MX191.3, R191.1
unnamed: D1092.1 (K), MX192.3, MX192_2.3, R192.1
unnamed: D1094.1 (K), MX194.3, R194.1
unnamed: D1095.1 (K), MX195.3, R195.1
unnamed: D1096.1 (K), MX196.3, R196.1
unnamed: D1097.1 (K), MX197.3, R197.1
unnamed: D1098.1 (K), MX198.3, MX198_2.3, R198.1
unnamed: D1099.1 (K), MX199.3, R199.1
unnamed: D1100.1 (K), MX200.3, R200.1
unnamed: D1101.1 (K), MX201.3, R201.1
unnamed: D1102.1 (K), MX202.3, R202.1
unnamed: D1104.1 (K), MX204.3, R204.1
unnamed: D1105.1 (K), MX205.3, R205.1
unnamed: D1106.1 (K), MX206.3, R206.1
unnamed: D1107.1 (K), MX207.3, R207.1
unnamed: D1108.1 (K), MX208.3, MX208_2.3, R208.1
unnamed: D1109.1 (K), MX209.3, R209.1
unnamed: D1110.1 (K), MX210.3, R210.1
unnamed: J4.5 (Shield), JUSB4.2
unnamed: J11.1 (VBUS), J111.1
unnamed: J11.4 (GND), J111.4
unnamed: J12.1 (VBUS), J222.1
unnamed: J12.4 (GND), J222.4
unnamed: J13.1 (VBUS), J333.1
unnamed: J13.4 (GND), J333.4
unnamed: JUSB1.2, USB1.6 (Shield)
unnamed: JUSB2.2, USB2.6 (Shield)
unnamed: JUSB3.2, USB3.0 (SHIELD)
unnamed: LED1.2 (A), LED1_2.2 (A), R6.1
unnamed: LED2.2 (A), LED2_2.2 (A), R7.1
unnamed: LED3.2 (A), LED3_2.2 (A), R8.1
unnamed: LED4.2 (A), R9.1
unnamed: LED5.2 (A), R10.1
unnamed: MX151.3, MX151_2.3, MX151_3.3, R151.1
unnamed: MX152.3, MX152_2.3, MX152_3.3, MX152_4.3, R152.1
unnamed: MX153.3, MX153_2.3, MX153_3.3, R153.1
unnamed: MX154.3, MX154_2.3, MX154_3.3, R154.1
unnamed: MX156.3, MX156_2.3, MX156_3.3, R156.1
unnamed: MX157.3, MX157_2.3, MX157_3.3, R157.1
unnamed: MX158.3, MX158_2.3, MX158_3.3, MX158_4.3, R158.1
unnamed: MX159.3, MX159_2.3, MX159_3.3, R159.1
unnamed: R3.2, U1.33 ((~HWB~)PE2), U1_2.33 ((~HWB~)PE2)
unnamed: RGBLED1.1 (DOUT), RGBLED2.3 (DIN)
unnamed: RGBLED2.1 (DOUT), RGBLED3.3 (DIN)
unnamed: RGBLED3.1 (DOUT), RGBLED4.3 (DIN)
unnamed: U1.42 (AREF), U1_2.42 (AREF)
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
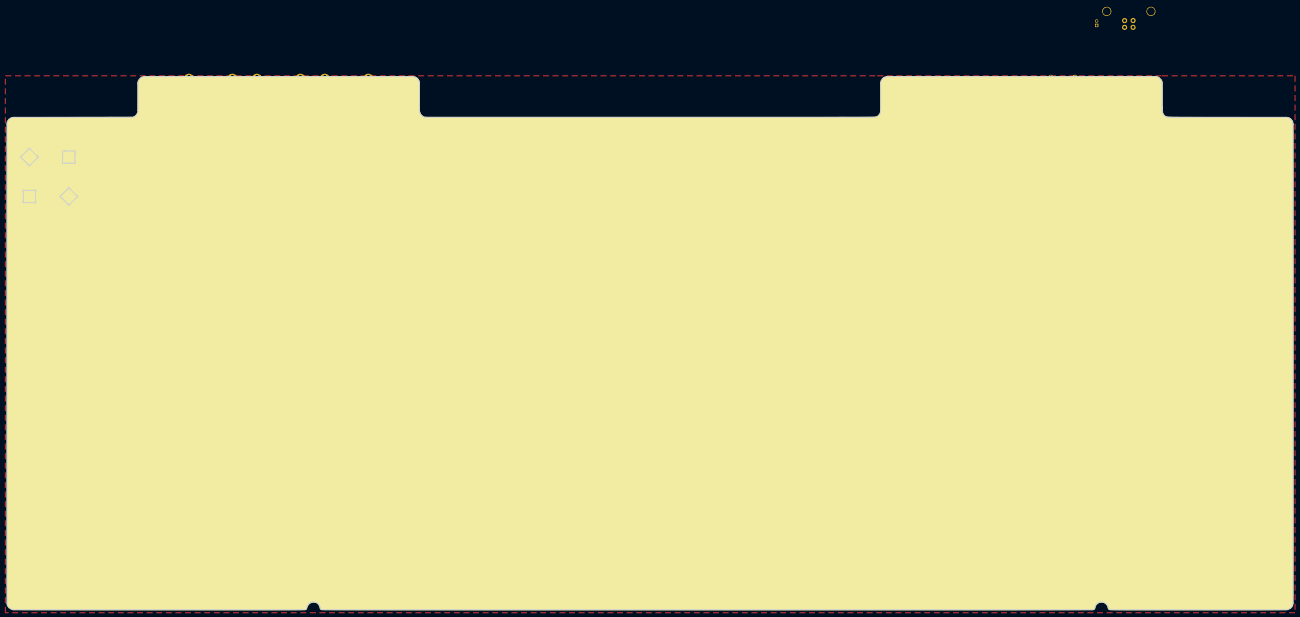
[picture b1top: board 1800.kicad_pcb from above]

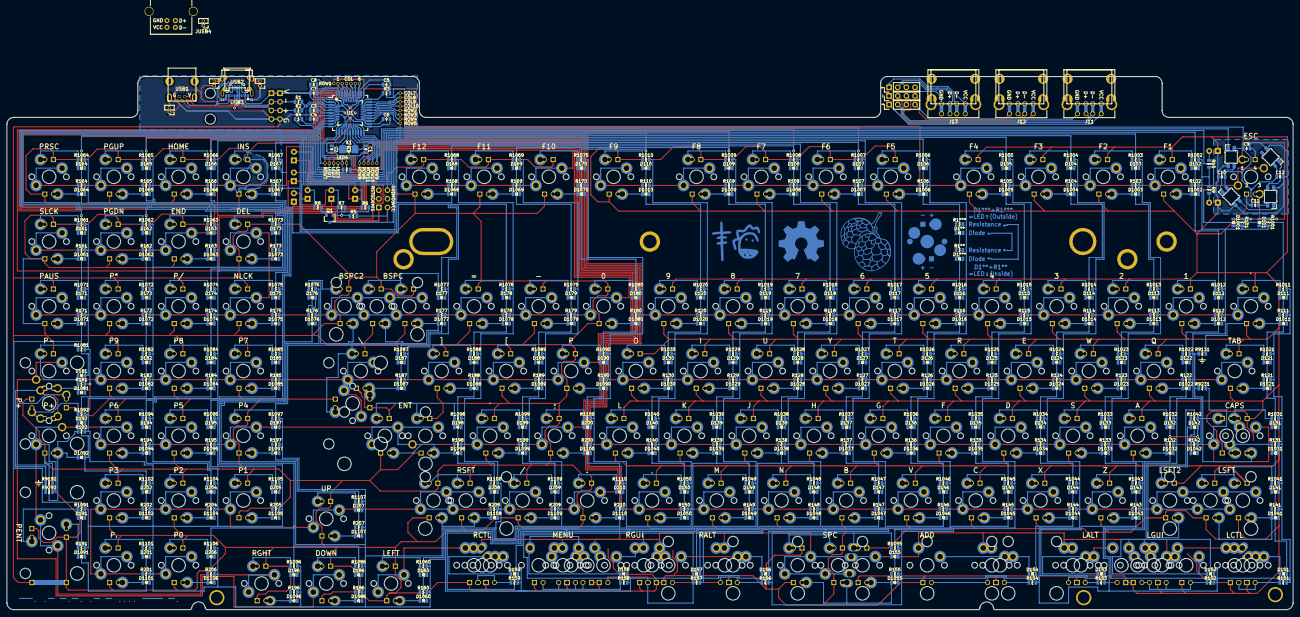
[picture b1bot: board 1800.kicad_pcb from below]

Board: 2 copper layers, 378.4 x 156.9 mm, 611 parts (461 on the bottom side), 276 nets.

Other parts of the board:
D1**, D1***: D_0805
J1#2: CONN_01X04; Pin_Header_Straight_1x04_Pitch2.54mm
R1**, R1***: R_0805
Ref**: CherryMX; MX1A&LEDx2

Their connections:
/USBD+: J1#2.3; also elsewhere on the board
/USBD-: J1#2.2; also elsewhere on the board
GND: J1#2.4; also elsewhere on the board
VCC: J1#2.1; also elsewhere on the board
